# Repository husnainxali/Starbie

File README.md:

# Starbie

 A Esp32_C3 based digital pet that u can play with and keep it alive if u dont it dies (x_x) ,sad thats why u have to keep it alive 

## Description
Starbie is a device made for digital pet I heavily referenced Tamagotchi and similar device I used a Esp32c3 microcontroller as the brain of the device and added DHT11 so it could sense the temprature around it and I added MPU6050 so it could feel movements and react to it 

### Screenshots

- **Schematic**

- **Pcb layout**

- **Pcb**

_ **Case**

## Getting Started
Full parts list with quantities and costs: **[BOM.csv](BOM.csv)**
first Download PCB files and edit them according your use and then order pcb
then solder all the components on the pcb board
and then flash it with the firmware add changes to it according to your need
3d print the case for it or don't use one. Its on u!

### Dependencies

#Libraries.

Open Sketch → Include Library → Manage Libraries. Install these libraries one at a time:

- **Adafruit GFX Library**
 
- **Adafruit SSD1306**

- **Adafruit MPU6050**

- **DHT sensor library**

If Arduino asks to install dependencies, choose Install All.

### Installing
- **Install the current **[Arduino IDE](https://www.arduino.cc/en/software)**.**

- **Open File → Preferences. In Additional Boards Manager URLs, add:**

https://espressif.github.io/arduino-esp32/package_esp32_index.json

- **Open Tools → Board → Boards Manager, search for esp32, and install esp32 by Espressif Systems.**

- **Under Tools → Board → esp32, select XIAO_ESP32C3.**

### Executing program

After installing ESp32 board and all the libraries open the **[Firmware.ino](Firmware/Starbie_firmware.ino)** file
When you get your board, click Arduino's arrow-shaped Upload button.

## License

This project is licensed under the MIT License - see the **[LICENSE](LICENSE)** file for details

----

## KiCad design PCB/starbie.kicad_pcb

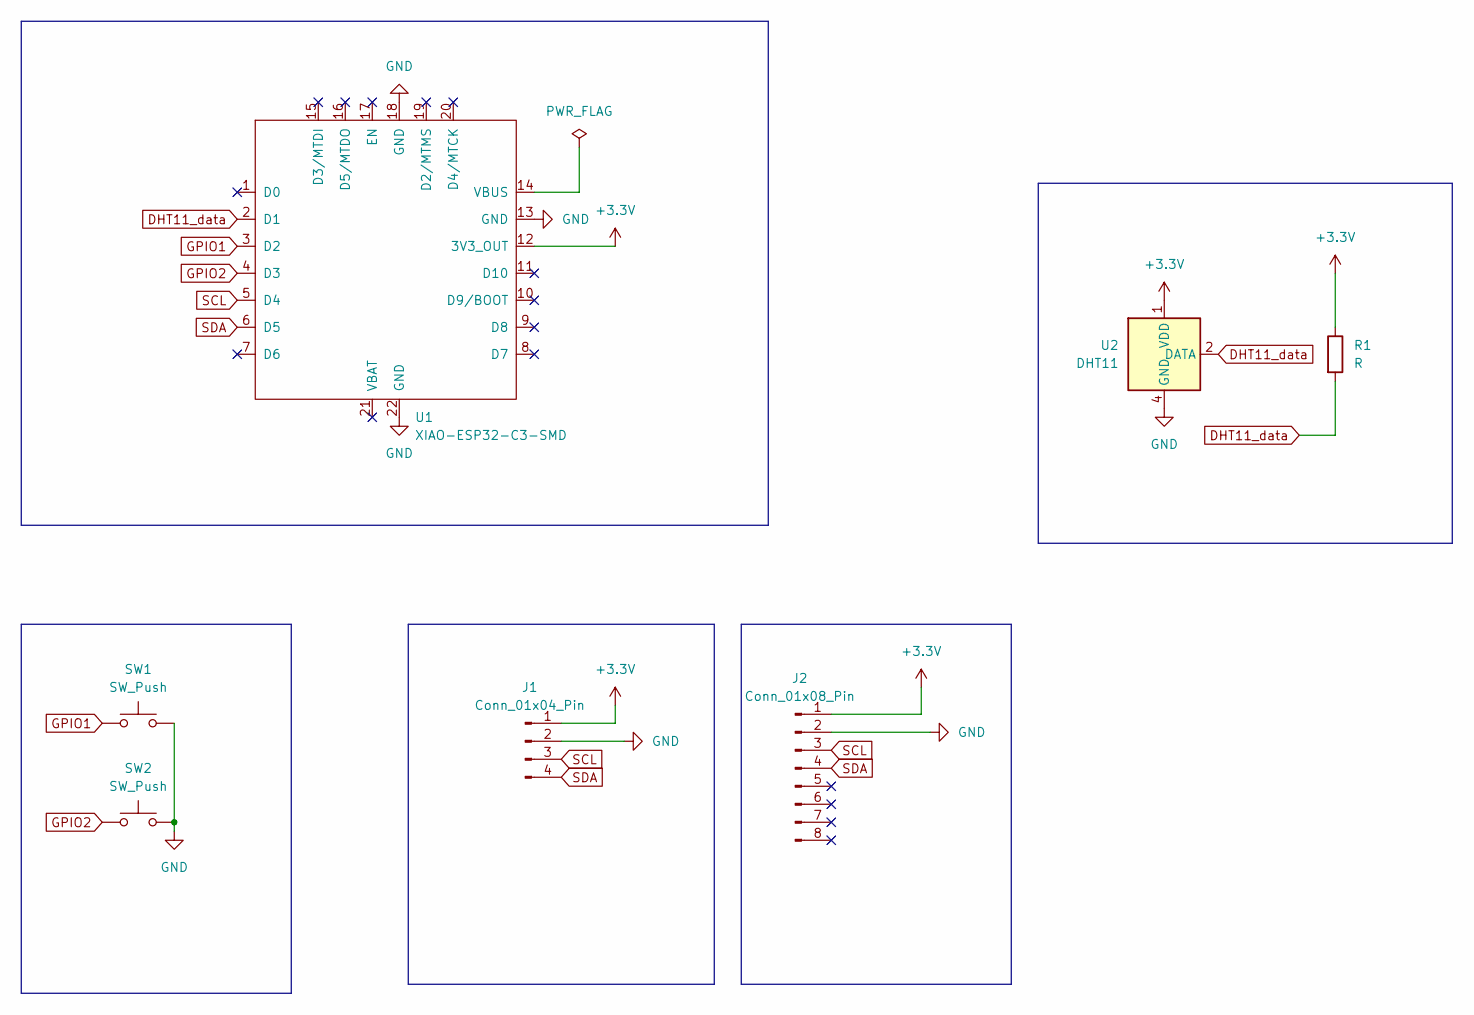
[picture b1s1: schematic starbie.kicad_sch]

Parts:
J1: Conn_01x04_Pin; Display_128x64_096_I2C
J2: Conn_01x08_Pin; PinHeader_1x08_P2.54mm_Vertical
R1: R; R_Axial_DIN0204_L3.6mm_D1.6mm_P7.62mm_Horizontal
SW1, SW2: SW_Push; SW_Cherry_MX_1.00u_PCB
U1: XIAO-ESP32-C3-SMD
U2: DHT11; Aosong_DHT11_5.5x12.0_P2.54mm

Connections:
+3.3V: J1.1, J2.1, R1.1, U1.12 (3V3_OUT), U2.1 (VDD)
DHT11_data: R1.2, U1.2 (D1), U2.2 (DATA)
GND: J1.2, J2.2, SW1.2, SW2.2, U1.13 (GND), U1.18 (GND), U1.22 (GND), U2.4 (GND)
GPIO1: SW1.1, U1.3 (D2)
GPIO2: SW2.1, U1.4 (D3)
SCL: J1.3, J2.3, U1.5 (D4)
SDA: J1.4, J2.4, U1.6 (D5)

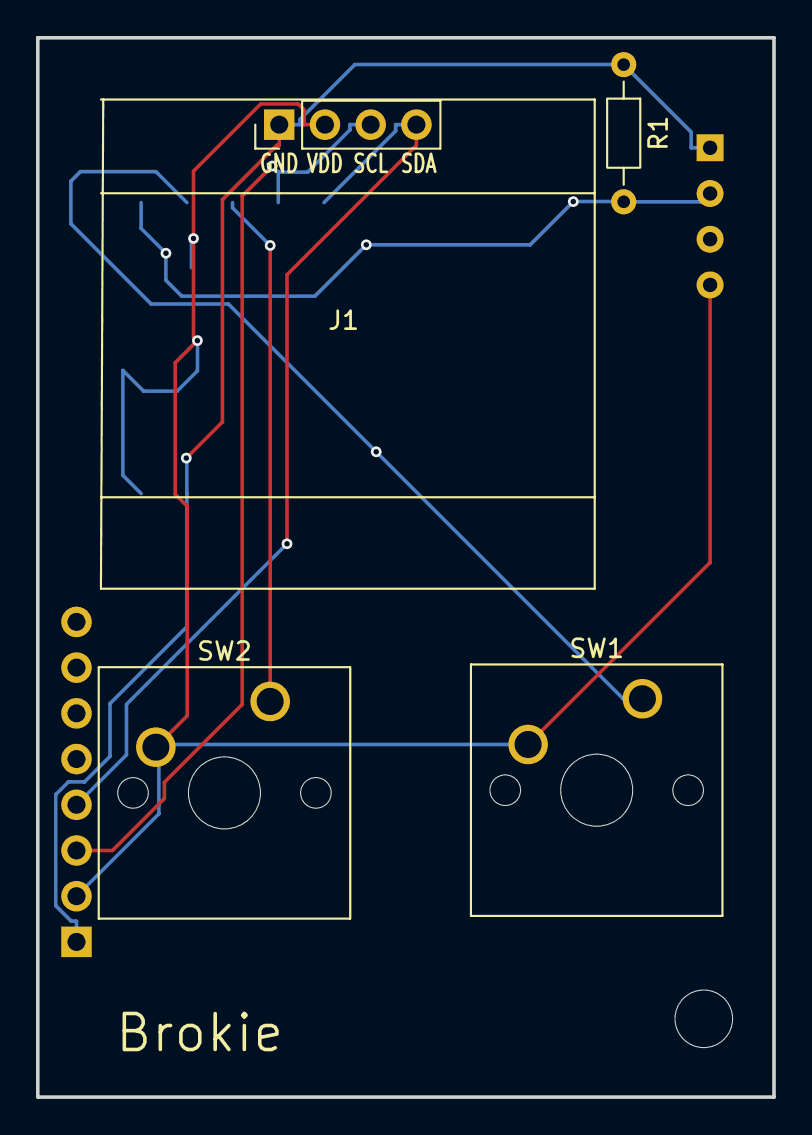
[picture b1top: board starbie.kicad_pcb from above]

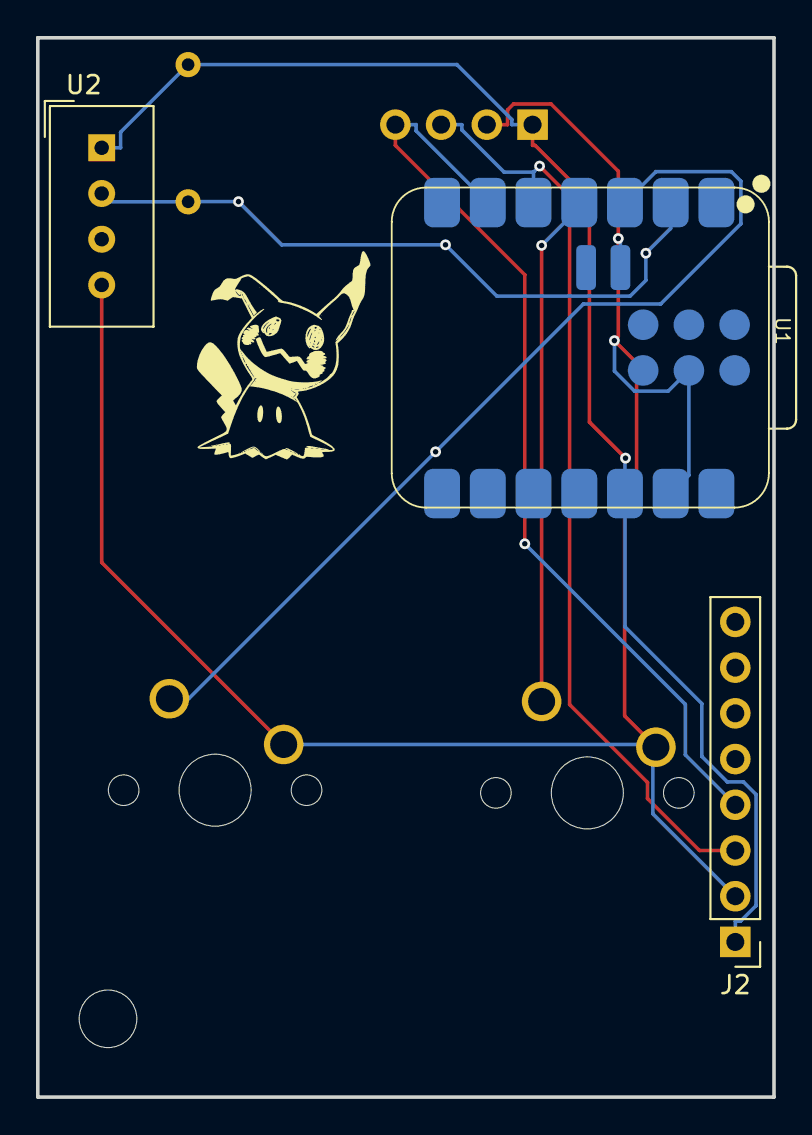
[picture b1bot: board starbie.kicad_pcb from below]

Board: 2 copper layers, 40.9 x 58.8 mm, 7 parts (3 on the bottom side), 7 nets.
